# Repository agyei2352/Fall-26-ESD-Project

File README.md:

# Wearable Smart ESD Wristband Monitor (Stage 1)

> [!NOTE]
> ### Engineering Portfolio & Technical Archive Notice
> **Development Context:** This project was engineered, modeled, and verified prior to publication as an academic/R&D milestone at the University of North Texas.  
> **Toolchain:** Primary development, embedded firmware scripting, and project integration were executed locally in **VS Code**, alongside native engineering design suites (**KiCad 10**, **SolidWorks**, **NI Multisim 14.3**, and **MATLAB**).  
> **Repository Purpose:** This repository serves as an **external public portfolio and verification archive** for engineering recruiters, hiring managers, and interviewers to inspect the design files, source code, schematics, 3D CAD models, and simulation data.

---

## Project Overview

A wearable, continuous dual-wire ESD (Electrostatic Discharge) wristband integrity monitor engineered around a bare **Nordic Semiconductor nRF52840-QIAA (aQFN-73)** System-on-Chip and powered by a single **CR2032 primary coin cell** ($3.0\text{ V}$ nominal).

The device measures human skin contact impedance and wristband loop continuity in real-time to prevent ESD damage in sensitive semiconductor and medical device cleanroom environments according to **ANSI/ESD S20.20** specifications.

```
+-----------------------------------------------------------------------------------------+
|                               SYSTEM ARCHITECTURE DIAGRAM                               |
+-----------------------------------------------------------------------------------------+
|                                                                                         |
|   +-------------------+       +-----------------------+       +---------------------+   |
|   |  CR2032 Coin Cell | ----> | Nordic nRF52840 SoC   | ----> | Status LEDs / User  |   |
|   |  (3.0V, 225 mAh)  |       | (Arm Cortex-M4, BLE)  |       | (Good, Warn, Fail)  |   |
|   +-------------------+       +-----------------------+       +---------------------+   |
|                                       ^       |                                         |
|                                       |       v                                         |
|                             ADC Sense |       | Active Pulse                            |
|                                       |       | (P0.13)                                 |
|                               +-----------------------+                                 |
|                               | Dual-Wire ESD Strap   |                                 |
|                               | & Human Skin Divider  |                                 |
|                               +-----------------------+                                 |
+-----------------------------------------------------------------------------------------+
```

---

## Key Hardware & Engineering Specifications

- **Microcontroller / SoC:** Bare Nordic Semiconductor **nRF52840-QIAA (aQFN-73)** running at $64\text{ MHz}$ Arm Cortex-M4F with $1\text{ MB}$ Flash and $256\text{ KB}$ RAM.
- **Power Budget & Battery Life:** Powered by a Keystone 3002 retainer with a single CR2032 cell. Ultra-low power duty cycle ($250\text{ ms}$ active measurement, $800\text{ ms}$ system sleep at $<2\,\mu\text{A}$), enabling continuous multi-month operation.
- **PCB Layout (KiCad 10):** Custom 2-layer board ($32.0 \times 40.0\text{ mm}$), $1.6\text{ mm}$ FR4, $1\text{ oz}$ copper. Includes matched RF trace geometry, $32\text{ MHz}$ HFXO / $32.768\text{ kHz}$ LFXO reference crystals, SWD programming header, and a high-impedance $1\text{ M}\Omega$ active pulse / sense divider path. Achieved **0 ERC errors** and **0 DRC violations**.
- **Mechanical Enclosure (SolidWorks):** Parametric wearable housing ($36.6 \times 44.6 \times 12.1\text{ mm}$) featuring $20\text{ mm}$ strap lugs, toolless twist-lock battery door, and $\varnothing 2\text{ mm}$ optical light-pipe guides. Validated zero-collision fit via 3D STEP import.

---

## Operating Resistance Bands & Detection Logic

Continuous status classification is derived via an active pulse voltage divider sampled by the nRF52840 SAADC:

$$\text{ADC Voltage } V_{\text{sense}} = V_{\text{pulse}} \times \frac{R_{\text{ref}}}{R_{\text{ref}} + R_{\text{loop}}}$$

| Status Band | Measured Loop Resistance ($R_{\text{loop}}$) | Sense Voltage ($V_{\text{sense}}$) | Indicator Behavior | Physical Condition |
| :--- | :--- | :--- | :--- | :--- |
| **GOOD** | $< 5.0\text{ M}\Omega$ | $> 0.4286\text{ V}$ | Green LED active | Proper strap fit and skin contact |
| **WARNING** | $5.0\text{ M}\Omega \text{ to } 35.0\text{ M}\Omega$ | $0.0811\text{ V to } 0.4286\text{ V}$ | Yellow LED active | Dry skin, high impedance, loose fit |
| **FAIL** | $> 35.0\text{ M}\Omega$ | $< 0.0811\text{ V}$ | Red LED active | Open loop, disconnected strap, ungrounded |

---

## Repository Directory Structure

```text
smart-esd-wristband-monitor/
├── Arduino Code/                # Bare nRF52840 state machine & firmware (VS Code)
│   ├── ESD_Wristband_Firmware.ino
│   ├── firmware_timing_state_machine.png
│   └── README.md
├── Digital Circuit Data/        # NI Multisim 14.3 circuit, SPICE netlist, oscilloscope captures
│   ├── ESD Impedance Device.ms14
│   ├── ESD_Wristband_Multisim_Circuit.cir
│   ├── multisim_circuit_schematic.png
│   ├── multisim_oscilloscope_transient.png
│   └── README.md
├── MATLAB Model/                # Mathematical model, RC transient response, transfer curves
│   ├── esd_wristband_status_model.m
│   ├── ESD_Wristband_Calculation_Report.pdf
│   ├── matlab_pulse_response_plot.png
│   ├── matlab_adc_transfer_curve.png
│   └── README.md
├── PCB Design/                  # Native KiCad 10 project, 2-layer PCB layout, 3D renders, DRC
│   ├── ESD_Wristband_Monitor.kicad_pro / .kicad_sch / .kicad_pcb
│   ├── ESD_Wristband_Monitor.step
│   ├── board_render_3d.png
│   ├── board_render_top.png
│   ├── erc_report.rpt (0 Errors, 0 Warnings)
│   ├── drc_report.rpt (0 Shorts, 0 Clearance Errors)
│   └── README.md
├── SolidWorks Design/           # 3D printable mechanical enclosure, strap lugs, and battery bay
│   ├── Complete_Enclosure_Assembly.stl  (Viewable in GitHub 3D viewer)
│   ├── Enclosure_Top_Cover.stl
│   ├── Enclosure_Bottom_Base.stl
│   ├── Battery_Door.stl
│   ├── ESD_Wristband_Monitor_PCB.step
│   └── README.md
├── Wokwi/                       # Interactive firmware logic verification & sweep data
│   ├── sketch.ino
│   ├── wokwi_wiring_diagram.png
│   └── README.md
├── Parts List/                  # Stage 1 BOM with MPNs and footprints
│   └── README.md
├── Project Requirements/        # ANSI/ESD S20.20 standards and specifications
│   └── README.md
├── Test Results/                # Verification logs and potentiometer sweep matrices
│   └── README.md
└── Stage 1 Plan and Learning Resources.md # Engineering plan and Stage 2 hardware roadmap
```

---

## Stage 1 Verification & Testing Matrix

| Tool / Environment | Engineering Role | Key Output / Verification Metric | Visual Asset |
| :--- | :--- | :--- | :--- |
| **VS Code / Arduino** | State machine firmware & timing control | $250\text{ ms}$ pulse / $800\text{ ms}$ sleep state cycle | [`firmware_timing_state_machine.png`](Arduino%20Code/firmware_timing_state_machine.png) |
| **KiCad 10** | Schematic capture & 2-layer PCB layout | Passed ERC (0 errors) and DRC (0 violations) | [`board_render_3d.png`](PCB%20Design/board_render_3d.png) |
| **SolidWorks** | Enclosure CAD & 3D print validation | Zero-collision assembly mating via STEP | [`SolidWorks Design/`](SolidWorks%20Design/README.md) |
| **MATLAB** | Mathematical RC transient modeling | Calculated $V_{\text{plateau}}$, $\tau$, and settling curve | [`matlab_pulse_response_plot.png`](MATLAB%20Model/matlab_pulse_response_plot.png) |
| **NI Multisim** | SPICE circuit simulation | Verified node voltage transient response | [`multisim_circuit_schematic.png`](Digital%20Circuit%20Data/multisim_circuit_schematic.png) |
| **Wokwi** | Hardware logic prototype sweep | Verified Good/Warning/Fail transitions | [`wokwi_wiring_diagram.png`](Wokwi/wokwi_wiring_diagram.png) |

---

## How to Review & Inspect Files

- **View 3D Enclosure:** Click on [`SolidWorks Design/Complete_Enclosure_Assembly.stl`](SolidWorks%20Design/Complete_Enclosure_Assembly.stl) to inspect the 3D model directly in GitHub's native 3D browser viewer.
- **Inspect Firmware:** Open [`Arduino Code/ESD_Wristband_Firmware.ino`](Arduino%20Code/ESD_Wristband_Firmware.ino) to review the bare nRF52840 register configuration, SAADC sampling, and sleep timing logic.
- **Inspect PCB Design:** Open `PCB Design/ESD_Wristband_Monitor.kicad_pro` using **KiCad 10** to view schematic sheets, design rules, and copper routing.
- **Review Circuit SPICE Simulation:** Open `Digital Circuit Data/ESD Impedance Device.ms14` in **NI Multisim 14.3** or inspect the netlist in `Digital Circuit Data/ESD_Wristband_Multisim_Circuit.cir`.

---

## License & Intellectual Property

Copyright &copy; 2026 Prince Agyei. All Rights Reserved.  
This project and all associated design assets (firmware, schematics, PCB layouts, 3D CAD models, and simulation files) are published strictly for recruiter portfolio review and academic verification. Unauthorized copying, physical fabrication, modification, or commercial distribution is prohibited. See [`LICENSE`](LICENSE) for complete terms.

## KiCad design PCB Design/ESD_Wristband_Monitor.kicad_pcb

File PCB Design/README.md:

# PCB Design (KiCad 10)

This directory contains the editable KiCad 10 project, manufacturing files, and 3D mechanical handoff models for the bare **Nordic nRF52840-QIAA (aQFN-73)** wearable ESD wristband monitor.

---

## 1. Visual Board Renders

### A. 3D Perspective Isometric Render
Raytraced 3D view showing the physical component placement, bare SoC, crystals, status LEDs, programming header, and inverted-F PCB antenna:

### B. 2D Top Copper & Silkscreen Render
Top-down orthographic view of the $32.0 \times 40.0\text{ mm}$ 2-layer board layout:

---

## 2. Stage 1 Deliverables Summary

| File | Type | Description |
| :--- | :--- | :--- |
| [`ESD_Wristband_Monitor.kicad_pro`](file:///C:/Fall%2026%20ESD%20Project/PCB%20Design/ESD_Wristband_Monitor.kicad_pro) | KiCad Project | Master KiCad 10 project control file |
| [`ESD_Wristband_Monitor.kicad_sch`](file:///C:/Fall%2026%20ESD%20Project/PCB%20Design/ESD_Wristband_Monitor.kicad_sch) | KiCad Schematic | Schematic architecture with bare nRF52840-QIAA |
| [`ESD_Wristband_Monitor.kicad_pcb`](file:///C:/Fall%2026%20ESD%20Project/PCB%20Design/ESD_Wristband_Monitor.kicad_pcb) | KiCad Board | $32 \times 40\text{ mm}$ 2-layer layout with official Nordic footprints & nets |
| [`ESD_Wristband_Monitor.step`](file:///C:/Fall%2026%20ESD%20Project/PCB%20Design/ESD_Wristband_Monitor.step) | 3D STEP Model | AP214 STEP mechanical CAD model for SolidWorks enclosure integration |
| [`erc_report.rpt`](file:///C:/Fall%2026%20ESD%20Project/PCB%20Design/erc_report.rpt) | ERC Log | Electrical Rules Check report (**0 Errors, 0 Warnings**) |
| [`drc_report.rpt`](file:///C:/Fall%2026%20ESD%20Project/PCB%20Design/drc_report.rpt) | DRC Log | Design Rules Check report (**0 Shorts, 0 Clearance Errors**) |
| [`generate_kicad_project.py`](file:///C:/Fall%2026%20ESD%20Project/PCB%20Design/generate_kicad_project.py) | Python Script | Standalone automated generator using official KiCad 10 `pcbnew` Python API |

---

## 3. Nordic Reference Circuit & Hardware Implementation

The design adheres strictly to **Nordic Semiconductor nRF52840 Product Specification v1.11 / v1.12, Section 7.3 (Circuit Configuration No. 2 for QIAA aQFN-73)**:

1. **Power Configuration (Normal Voltage Mode):**
   - Supply: Single CR2032 primary coin cell ($3.0\text{ V}$ nominal, $1.7\text{--}3.6\text{ V}$ operational).
   - High-voltage regulator REG0 bypassed by shorting `VDDH` (Pin Y2) directly to `VDD` (Pins B1, W1, A22, AD14, AD23).
   - `VBUS` (Pin AD2) tied directly to ground (USB powered down, no charger circuit).
2. **Internal REG1 DC/DC Converter:**
   - DC/DC switching inductor $L_2$ ($10\,\mu\text{H}$, 0603) placed between `DCC` (Pin B3) and `DEC4_6` to reduce active current from the coin cell by up to $50\%$.
3. **Mandatory Silicon Bridge (`DEC4_6`):**
   - `DEC4` (Pin B5) and `DEC6` (Pin E24) must be shorted together externally on the PCB with a $1.0\,\mu\text{F}$ decoupling capacitor ($C_4$) to ground to supply the 2.4 GHz radio synthesizer.
4. **RF Matching Network & Antenna:**
   - Single-ended $50\,\Omega$ Pi-network on pin `ANT` (H23):
     - Series inductor: $L_1 = 3.9\text{ nH}$ (0402)
     - Shunt capacitors: $C_{12} = 1.2\text{ pF}$ (0402) and $C_{13} = 1.5\text{ pF}$ (0402)
     - Inverted-F quarter-wave PCB trace antenna routed along the top board edge with ground plane clearance.
5. **Crystals:**
   - High Frequency: $32.0\text{ MHz}$ crystal ($X_1$) with two $12\text{ pF}$ load capacitors ($C_1, C_2$) on pins `XC1`/`XC2`.
   - Low Frequency: $32.768\text{ kHz}$ tuning fork crystal ($X_2$) with two $12\text{ pF}$ load capacitors ($C_{14}, C_{15}$) on pins `XL1`/`XL2`.

---

## 4. ERC & DRC Full Verification Summary

### Electrical Rules Check (`erc_report.rpt`):
- **Errors:** 0
- **Warnings:** 0
- **Status:** **PASS**

### Design Rules Check (`drc_report.rpt`):
- **Short Circuits:** 0
- **Clearance Violations:** 0
- **Courtyard Overlaps:** 0
- **Unconnected Pads:** 71 (unrouted ratline nets ready for interactive routing)
- **Dangling Tracks:** 2 (Antenna open monopole tip + RF entry tap)
- **Silkscreen Clearances:** 5 minor label margin warnings

---

## 5. Engineering Analysis & Review Documents

- [Stage 1 KiCad Proposal and Open Decisions](Stage%201%20KiCad%20Proposal%20and%20Open%20Decisions.md): Detailed circuit proposal, complete BOM, and 4 flagged hardware review items.
- [SAADC Interface Review](SAADC%20Interface%20Review.md): Analysis of source impedance ($1\text{ M}\Omega$) vs. Nordic $800\text{ k}\Omega$ guideline.

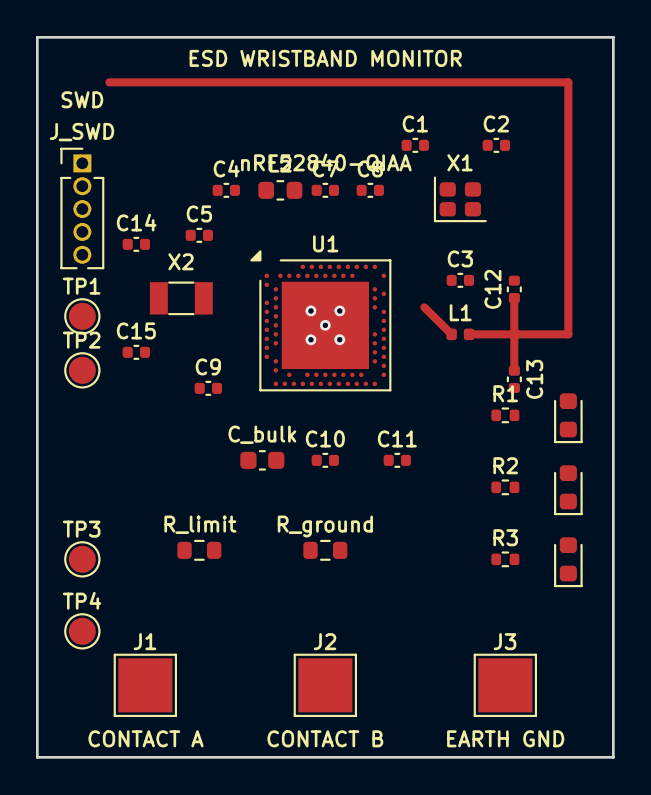
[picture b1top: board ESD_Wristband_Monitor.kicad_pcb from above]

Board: 2 copper layers, 32.0 x 40.0 mm, 37 parts (1 on the bottom side), 24 nets.

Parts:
BT1: CR2032; BatteryHolder_Keystone_3002_1x2032
C1, C2, C14, C15: 12pF; C_0402_1005Metric
C3: 100pF; C_0402_1005Metric
C4: 1.0uF; C_0402_1005Metric
C5, C7, C8, C9, C10, C11: 100nF; C_0402_1005Metric
C12: 1.2pF; C_0402_1005Metric
C13: 1.5pF; C_0402_1005Metric
C_bulk: 4.7uF; C_0603_1608Metric
D_FAIL: Red; LED_0603_1608Metric
D_GOOD: Green; LED_0603_1608Metric
D_WARN: Yellow; LED_0603_1608Metric
J1: Contact_A; TestPoint_Pad_3.0x3.0mm
J2: Contact_B; TestPoint_Pad_3.0x3.0mm
J3: Ground_Cord; TestPoint_Pad_3.0x3.0mm
J_SWD: SWD; PinHeader_1x05_P1.27mm_Vertical
L1: 3.9nH; L_0402_1005Metric
L2: 10uH; L_0603_1608Metric
R1, R2, R3: 1.5k; R_0402_1005Metric
R_ground: 1.0M; R_0603_1608Metric
R_limit: 1.0M; R_0603_1608Metric
TP1: TP_PULSE; TestPoint_Pad_D1.5mm
TP2: TP_SENSE; TestPoint_Pad_D1.5mm
TP3: TP_VDD; TestPoint_Pad_D1.5mm
TP4: TP_GND; TestPoint_Pad_D1.5mm
U1: nRF52840-QIAA; Nordic_AQFN-73-1EP_7x7mm_P0.5mm
X1: 32MHz; Crystal_SMD_2016-4Pin_2.0x1.6mm
X2: 32.768kHz; Crystal_SMD_3215-2Pin_3.2x1.5mm

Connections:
+3V0: BT1.1, C7.1, C8.1, C9.1, C10.1, C11.1, C_bulk.1, J_SWD.1, TP3.1, U1.A22, U1.AD14, U1.AD23, U1.B1, U1.W1, U1.Y2
ADC_SENSE: J2.1, R_ground.1, TP2.1, U1.A12
CONTACT_A: J1.1, R_limit.2
DCC_SW: L2.1, U1.B3
DEC1: C5.1, U1.C1
DEC3: C3.1, U1.D23
DEC4_6: C4.1, L2.2, U1.B5, U1.E24
GND: BT1.2, C1.2, C2.2, C3.2, C4.2, C5.2, C7.2, C8.2, C9.2, C10.2, C11.2, C12.2, C13.2, C14.2, C15.2, C_bulk.2, D_FAIL.1, D_GOOD.1, D_WARN.1, J3.1, J_SWD.5, R_ground.2, TP4.1, U1.AD2, U1.B7, U1.EP, U1.F23, X1.2, X1.4
HFXO_XC1: C1.1, U1.B24, X1.1
HFXO_XC2: C2.1, U1.A23, X1.3
LED_FAIL: R3.1, U1.AC11
LED_GOOD: R1.1, U1.AC9
LED_WARN: R2.1, U1.AD10
LFXO_XL1: C14.1, U1.D2, X2.1
LFXO_XL2: C15.1, U1.F2, X2.2
NET_D_FAIL: D_FAIL.2, R3.2
NET_D_GOOD: D_GOOD.2, R1.2
NET_D_WARN: D_WARN.2, R2.2
PULSE_DRIVE: R_limit.1, TP1.1, U1.AD8
RF_ANT: L1.1, U1.H23
RF_MATCH: C12.1, C13.1, L1.2
SWDCLK: J_SWD.3, U1.AA24
SWDIO: J_SWD.2, U1.AC24
~RESET: J_SWD.4, U1.AC13
